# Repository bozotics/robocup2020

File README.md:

## PCB Design Files

View .sch and .brd files interactively on [Inventhub!](https://inventhub.io/c/bozotics/robocup2020/tree/PCB)   

Included in this repo are design files for the various PCBs we use. We designed these in EAGLE thanks to [Autodesk's free education licences](https://www.autodesk.com/education/free-software/featured). 

The libraries used unfortunately cannot be shared due to Autodesk's library.io sharing limitations, however if you would like to view it do contact us! We would be happy to send a copy of the latest version, albeit without the included 3d models (again due to the library.io limitations).

Structure of this repository:
```
.
├── Datasheets # PDFs for the various parts we use
├── PCB2k20 # Design files for our PCBs
│   ├── Layer 1, 3, 4 # for Soccer Open
│   ├── PMW3360MouseSensor # for our Mouse Sensor breakout board
│   ├── RescueLS # for Rescue Line's light sensor breakout board
│   └── TPS5430 # for the buck converter breakout board
├── TestV3_2020
└── Rescue
```
Files for previous years can be found in our [other archived repositories](https://github.com/bozotics).

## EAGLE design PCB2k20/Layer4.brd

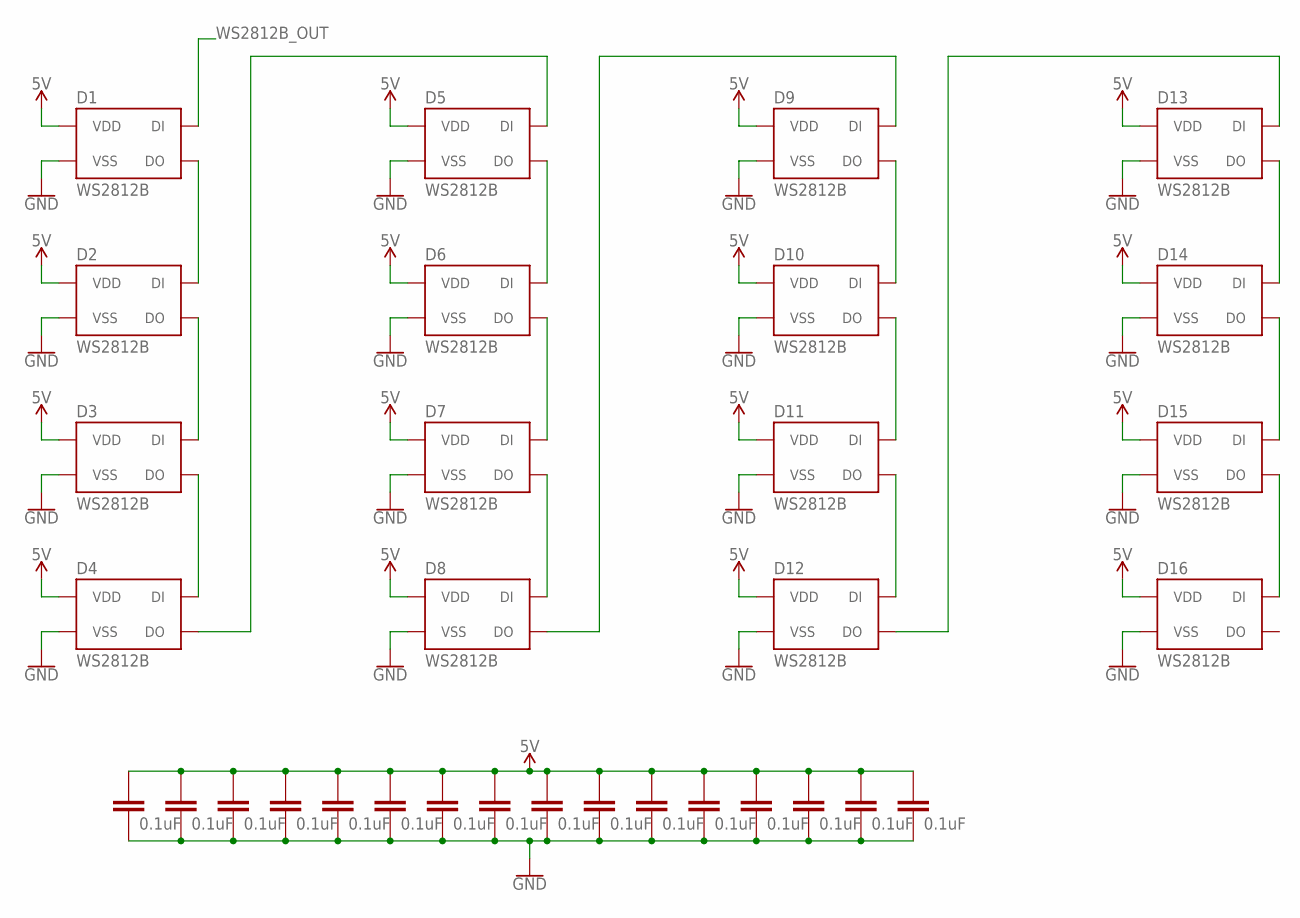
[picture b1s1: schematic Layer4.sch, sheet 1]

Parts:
AC1, AC2, AC3, AC4, AC5, AC6, AC7, AC8: 0.1uF; C0603
C1, C3, C5, C7, C9, C11, C13, C15: 0.1uF; C0603
D1, D2, D3, D4, D5, D6, D7, D8, D9, D10, D11, D12, D13, D14, D15, D16: WS2812B

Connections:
5V: AC1.1, AC2.1, AC3.1, AC4.1, AC5.1, AC6.1, AC7.1, AC8.1, C1.1, C3.1, C5.1, C7.1, C9.1, C11.1, C13.1, C15.1, D1.1 (VDD), D2.1 (VDD), D3.1 (VDD), D4.1 (VDD), D5.1 (VDD), D6.1 (VDD), D7.1 (VDD), D8.1 (VDD), D9.1 (VDD), D10.1 (VDD), D11.1 (VDD), D12.1 (VDD), D13.1 (VDD), D14.1 (VDD), D15.1 (VDD), D16.1 (VDD); also elsewhere on the board
GND: AC1.2, AC2.2, AC3.2, AC4.2, AC5.2, AC6.2, AC7.2, AC8.2, C1.2, C3.2, C5.2, C7.2, C9.2, C11.2, C13.2, C15.2, D1.3 (VSS), D2.3 (VSS), D3.3 (VSS), D4.3 (VSS), D5.3 (VSS), D6.3 (VSS), D7.3 (VSS), D8.3 (VSS), D9.3 (VSS), D10.3 (VSS), D11.3 (VSS), D12.3 (VSS), D13.3 (VSS), D14.3 (VSS), D15.3 (VSS), D16.3 (VSS); also elsewhere on the board
unnamed: D1.2 (DO), D2.4 (DI)
unnamed: D2.2 (DO), D3.4 (DI)
unnamed: D3.2 (DO), D4.4 (DI)
unnamed: D4.2 (DO), D5.4 (DI)
unnamed: D5.2 (DO), D6.4 (DI)
unnamed: D6.2 (DO), D7.4 (DI)
unnamed: D7.2 (DO), D8.4 (DI)
unnamed: D8.2 (DO), D9.4 (DI)
unnamed: D9.2 (DO), D10.4 (DI)
unnamed: D10.2 (DO), D11.4 (DI)
unnamed: D11.2 (DO), D12.4 (DI)
unnamed: D12.2 (DO), D13.4 (DI)
unnamed: D13.2 (DO), D14.4 (DI)
unnamed: D14.2 (DO), D15.4 (DI)
unnamed: D15.2 (DO), D16.4 (DI)
WS2812B_OUT: D1.4 (DI); also elsewhere on the board

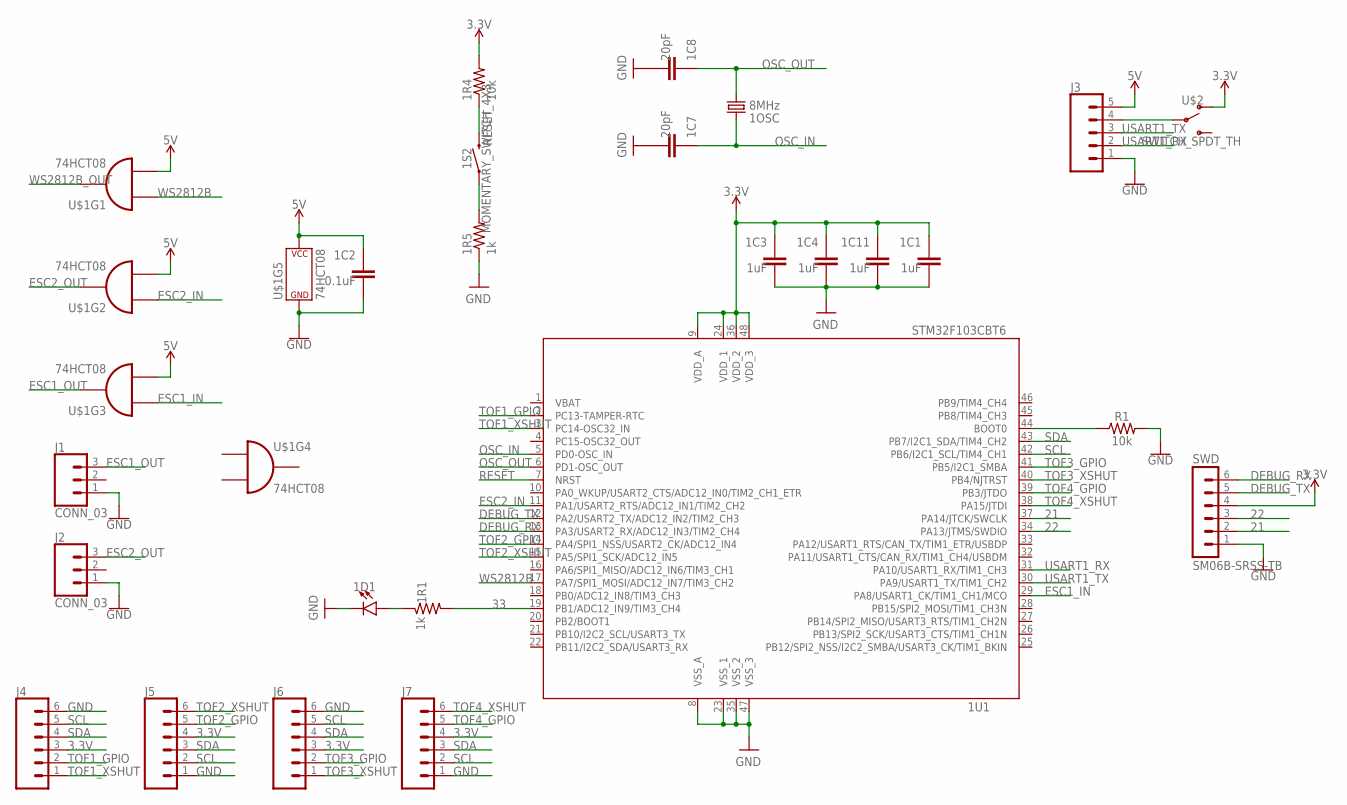
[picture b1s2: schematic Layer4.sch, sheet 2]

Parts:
1C1, 1C3, 1C4, 1C11: 1uF; C0603
1C2: 0.1uF; C0603
1C7, 1C8: 20pF; C0603
1D1: BLUE; LED-0603
1OSC: 8MHz; CRYSTAL-SMD-5X3.2-2PAD
1R1, 1R5: 1k; R0603
1R4: 10k; R0603
1S2: MOMENTARY_SWITCH_4X3
1U1: STM32F103CBT6; LQFP48
J1, J2: CONN_03; 1X03_LOCK
J3: CONN_05LOCK; 1X05_LOCK
J4, J5, J6, J7: CONN_06LOCK; 1X06_LOCK
R1: 10k; R0603
SWD: SM06B-SRSS-TB
U$1: 74HCT08; SOIC-14
U$2: SWITCH_SPDT_TH; SWITCH_SPDT_PTH_11.6X4.0MM_LOCK

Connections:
3.3V: 1C1.1, 1C3.1, 1C4.1, 1C11.1, 1R4.2, 1U1.9 (VDD_A), 1U1.24 (VDD_1), 1U1.36 (VDD_2), 1U1.48 (VDD_3), J4.3, J5.4, J6.3, J7.4, SWD.4, U$2.1 (O)
5V: 1C2.1, J3.5, U$1.P2 (I1), U$1.P5 (I1), U$1.P10 (I1), U$1.P14 (P$V+); also elsewhere on the board
21: 1U1.37 (PA14/JTCK/SWCLK), SWD.2
22: 1U1.34 (PA13/JTMS/SWDIO), SWD.3
33: 1R1.2, 1U1.19 (PB1/ADC12_IN9/TIM3_CH4)
DEBUG_RX: 1U1.13 (PA3/USART2_RX/ADC12_IN3/TIM2_CH4), SWD.6
DEBUG_TX: 1U1.12 (PA2/USART2_TX/ADC12_IN2/TIM2_CH3), SWD.5
ESC1_IN: 1U1.29 (PA8/USART1_CK/TIM1_CH1/MCO), U$1.P9 (I0)
ESC1_OUT: J1.3, U$1.P8 (O)
ESC2_IN: 1U1.11 (PA1/USART2_RTS/ADC12_IN1/TIM2_CH2), U$1.P4 (I0)
ESC2_OUT: J2.3, U$1.P6 (O)
GND: 1C1.2, 1C2.2, 1C3.2, 1C4.2, 1C7.2, 1C8.2, 1C11.2, 1D1.C, 1R5.1, 1U1.8 (VSS_A), 1U1.23 (VSS_1), 1U1.35 (VSS_2), 1U1.47 (VSS_3), J1.1, J2.1, J3.1, J4.6, J5.1, J6.6, J7.1, R1.2, SWD.1, U$1.P7 (P$V-); also elsewhere on the board
unnamed: 1D1.A, 1R1.1
unnamed: 1R5.2, 1S2.P$1 (1)
unnamed: 1U1.44 (BOOT0), R1.1
unnamed: J3.4, U$2.2
OSC_IN: 1C7.1, 1OSC.P$2 (2), 1U1.5 (PD0-OSC_IN)
OSC_OUT: 1C8.1, 1OSC.P$1 (1), 1U1.6 (PD1-OSC_OUT)
RESET: 1R4.1, 1S2.P$2 (2), 1U1.7 (NRST)
SCL: 1U1.42 (PB6/I2C1_SCL/TIM4_CH1), J4.5, J5.2, J6.5, J7.2
SDA: 1U1.43 (PB7/I2C1_SDA/TIM4_CH2), J4.4, J5.3, J6.4, J7.3
TOF1_GPIO: 1U1.2 (PC13-TAMPER-RTC), J4.2
TOF1_XSHUT: 1U1.3 (PC14-OSC32_IN), J4.1
TOF2_GPIO: 1U1.14 (PA4/SPI1_NSS/USART2_CK/ADC12_IN4), J5.5
TOF2_XSHUT: 1U1.15 (PA5/SPI1_SCK/ADC12_IN5), J5.6
TOF3_GPIO: 1U1.41 (PB5/I2C1_SMBA), J6.2
TOF3_XSHUT: 1U1.40 (PB4/NJTRST), J6.1
TOF4_GPIO: 1U1.39 (PB3/JTDO), J7.5
TOF4_XSHUT: 1U1.38 (PA15/JTDI), J7.6
USART1_RX: 1U1.31 (PA10/USART1_RX/TIM1_CH3), J3.2
USART1_TX: 1U1.30 (PA9/USART1_TX/TIM1_CH2), J3.3
VBAT: 1U1.1 (VBAT)
WS2812B: 1U1.17 (PA7/SPI1_MOSI/ADC12_IN7/TIM3_CH2), U$1.P1 (I0)
WS2812B_OUT: U$1.P3 (O); also elsewhere on the board

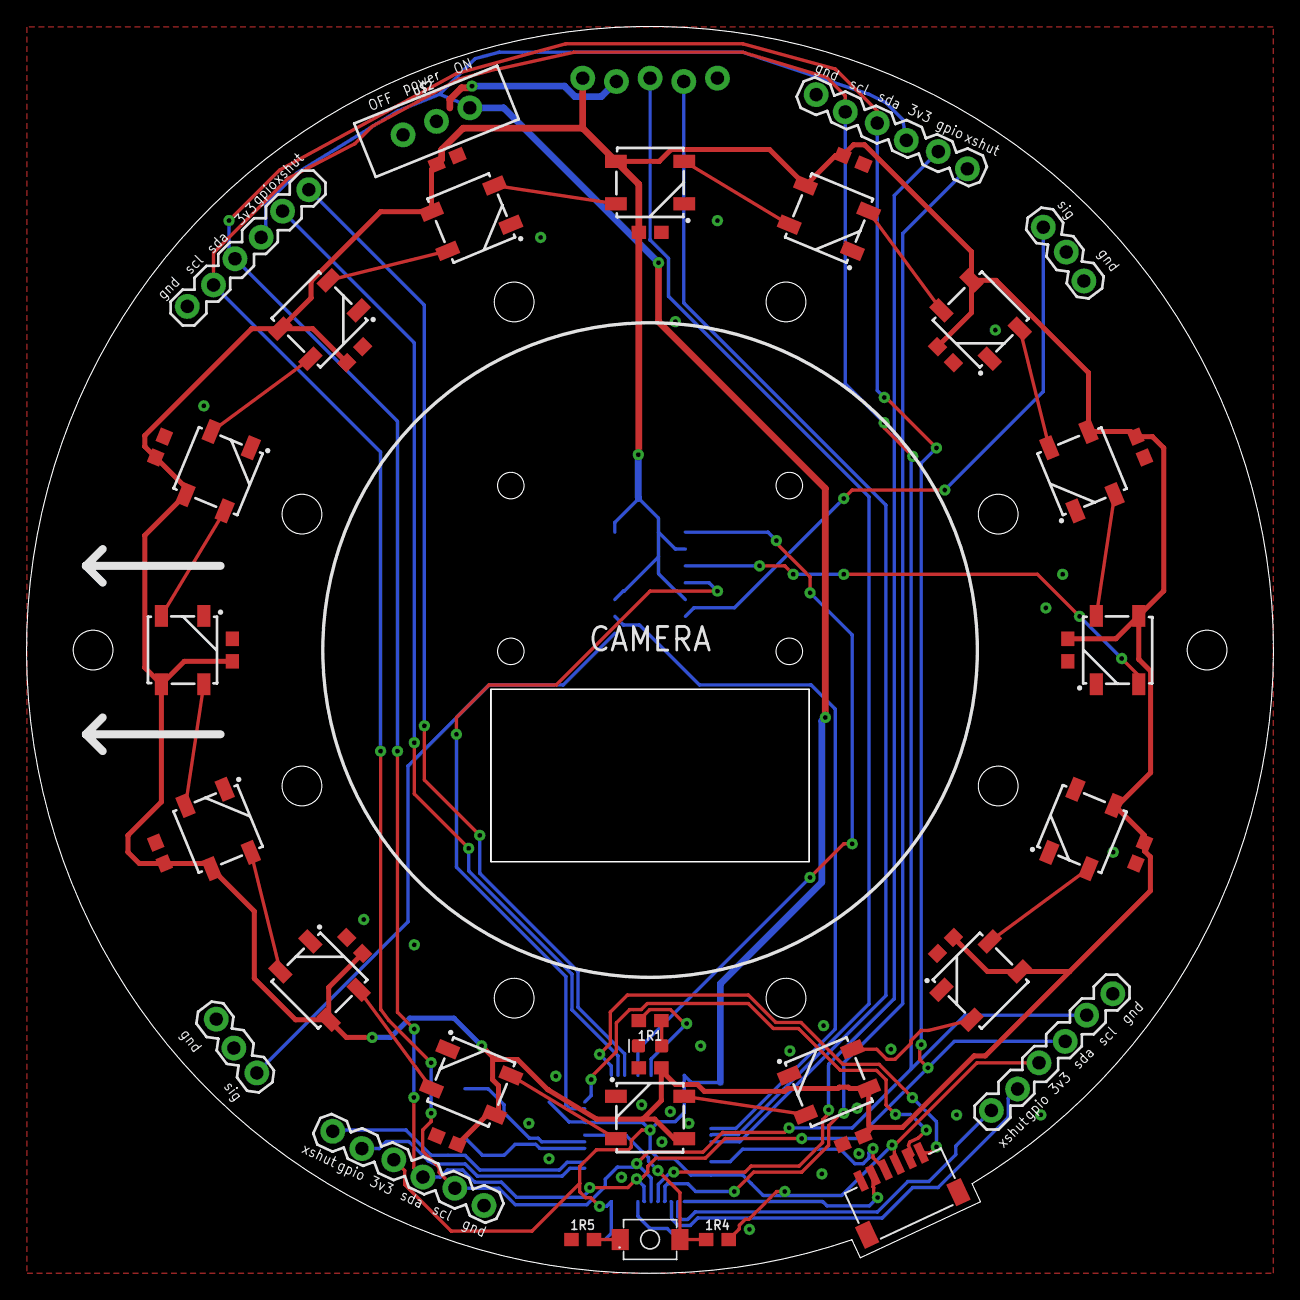
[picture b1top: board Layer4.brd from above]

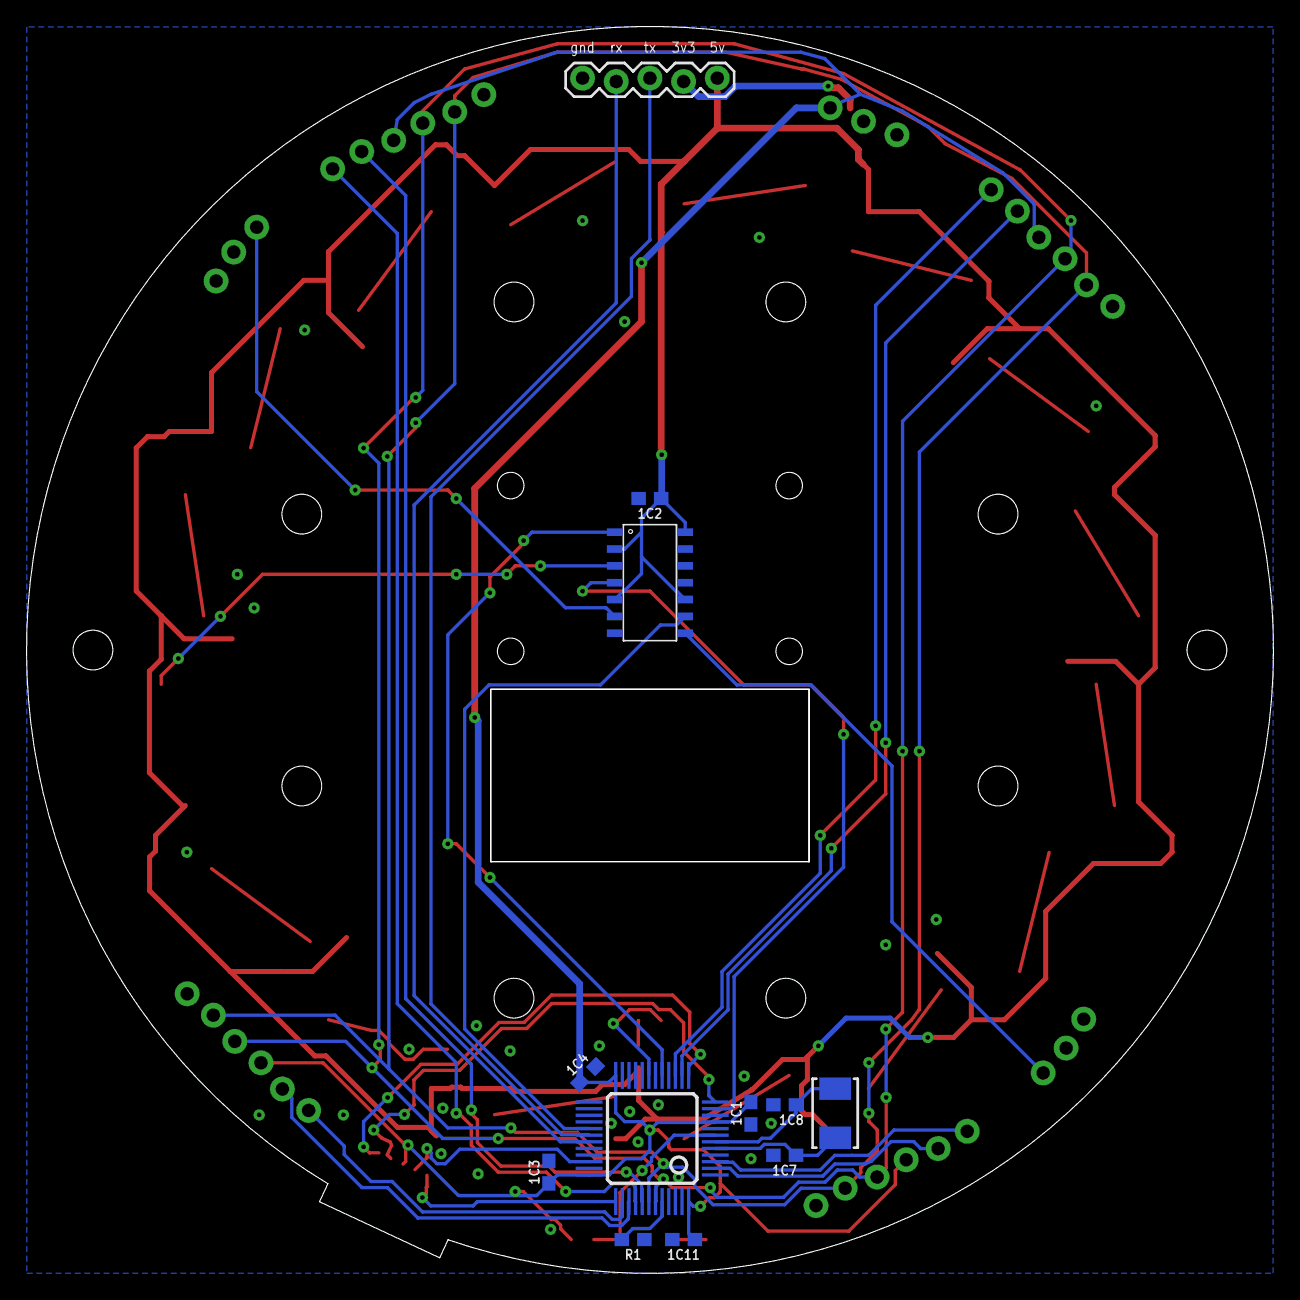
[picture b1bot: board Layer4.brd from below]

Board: 2 copper layers, 94.0 x 94.0 mm, 57 parts (12 on the bottom side), 48 nets.

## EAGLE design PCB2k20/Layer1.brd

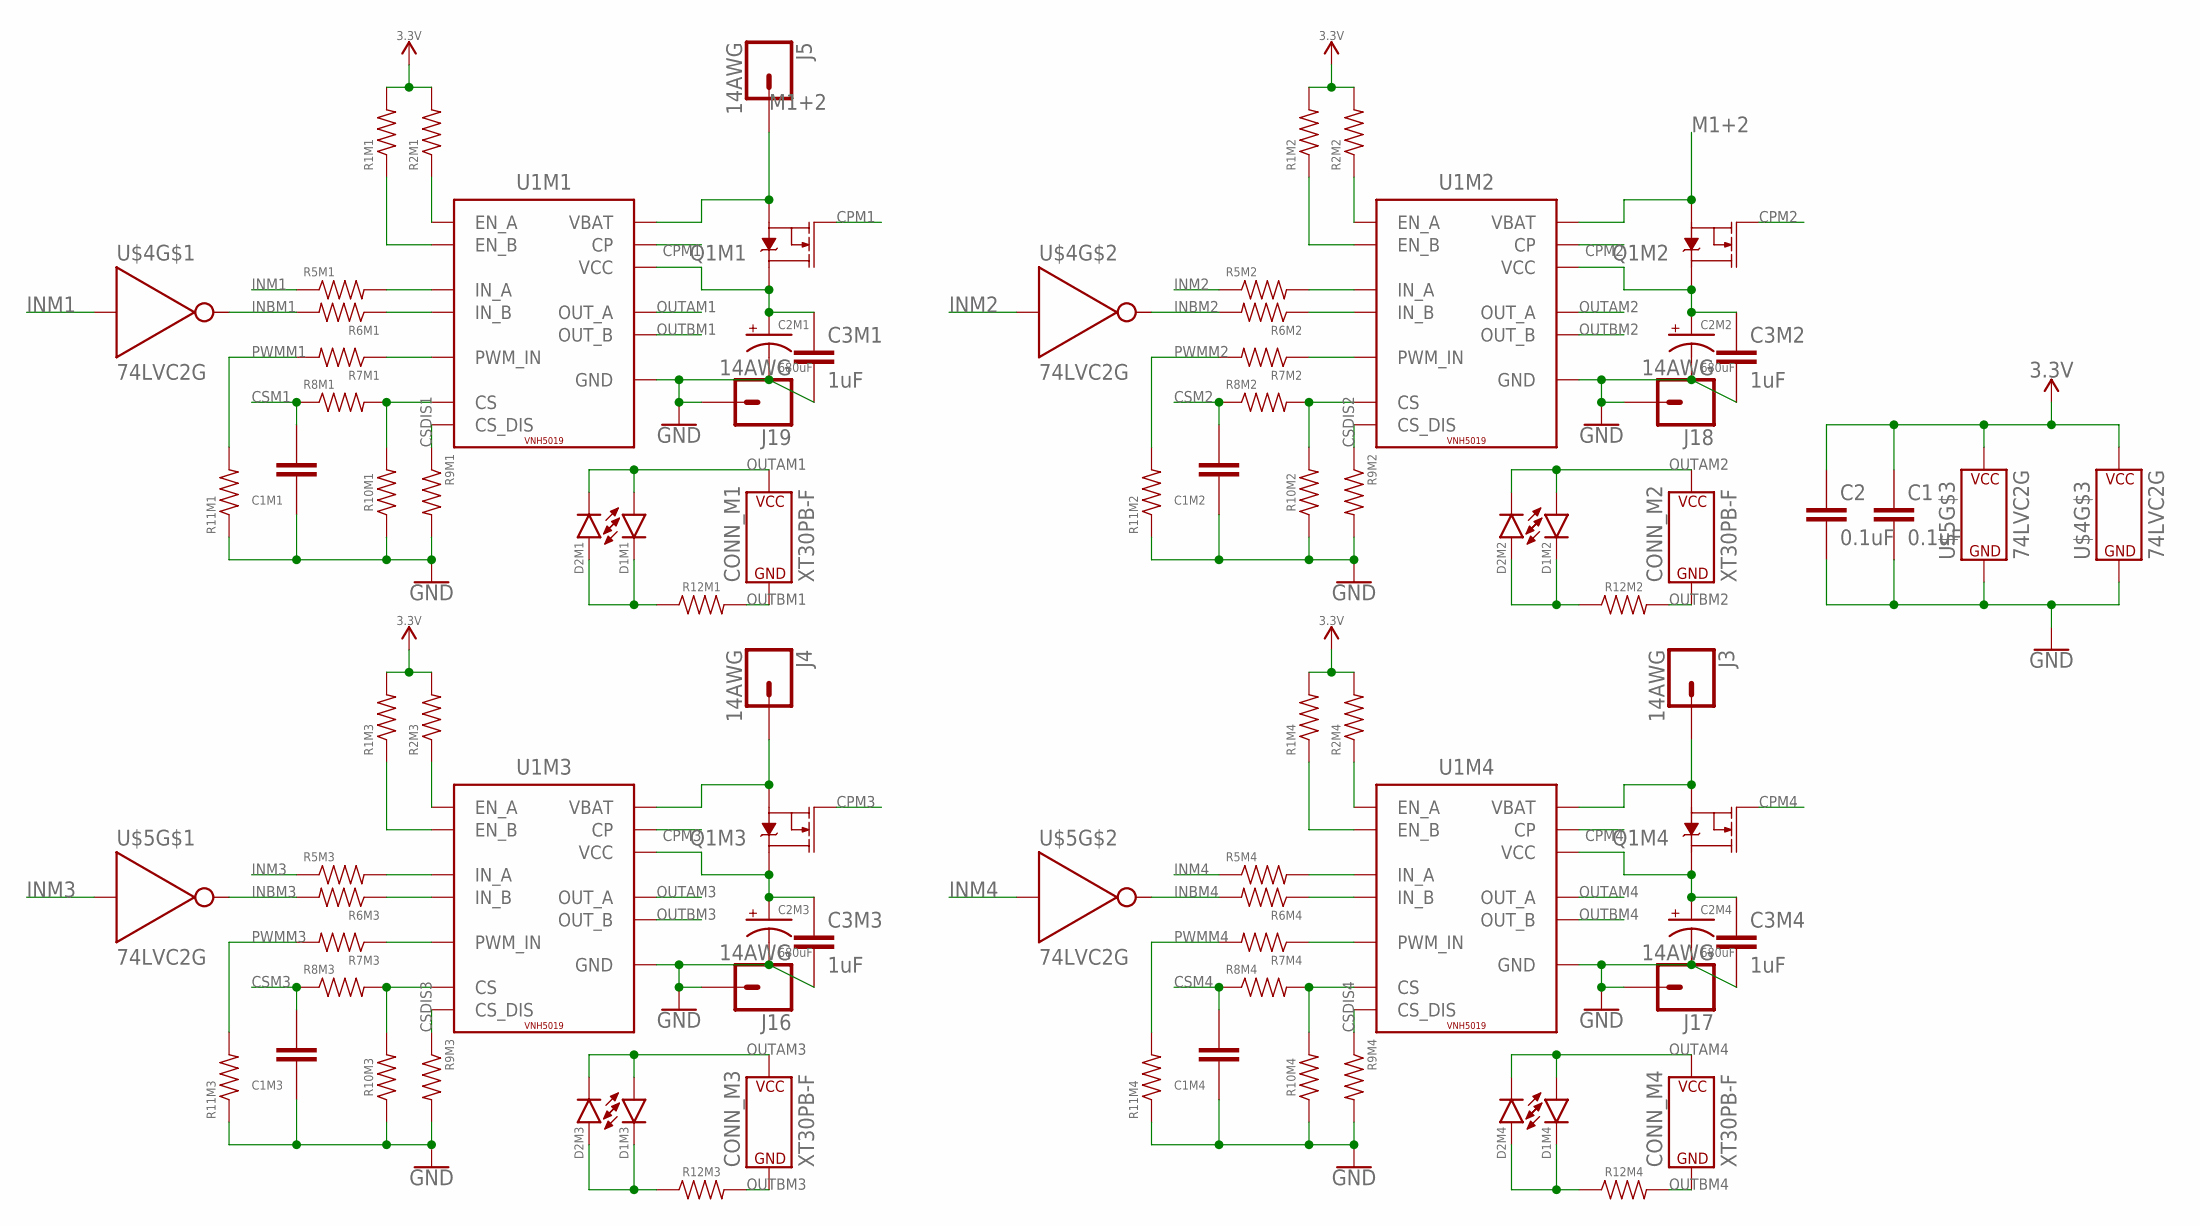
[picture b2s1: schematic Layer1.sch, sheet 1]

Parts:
C1, C2: 0.1uF; C0603
C1M1, C1M2, C1M3, C1M4: 33nF; C0603
C2M1, C2M2, C2M3, C2M4: 680uF; E3,5-8
C3M1, C3M2, C3M3, C3M4: 1uF; C0603
CONN_M1, CONN_M2, CONN_M3, CONN_M4: XT30PB-F
D1M1, D1M2, D1M3, D1M4: GREEN; LED-0603
D2M1, D2M2, D2M3, D2M4: RED; LED-0603
J3, J4, J5, J16, J17, J18, J19: 14AWG
Q1M1, Q1M2, Q1M3, Q1M4: AOD482; DPAK
R1M1, R1M2, R1M3, R1M4, R2M1, R2M2, R2M3, R2M4: 3.24k; R0603
R5M1, R5M2, R5M3, R5M4, R6M1, R6M2, R6M3, R6M4, R7M1, R7M2, R7M3, R7M4, R10M1, R10M2, R10M3, R10M4: 1k; R0603
R8M1, R8M2, R8M3, R8M4, R9M1, R9M2, R9M3, R9M4, R11M1, R11M2, R11M3, R11M4: 10k; R0603
R12M1, R12M2, R12M3, R12M4: 4.7k; R0603
U1M1, U1M2, U1M3, U1M4: VNH5019; POWERSO-30
U$4, U$5: 74LVC2G; SOT23-6

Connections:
3.3V: C1.1, C2.1, R1M1.2, R1M2.2, R1M3.2, R1M4.2, R2M1.2, R2M2.2, R2M3.2, R2M4.2, U$4.5 (P$V+), U$5.5 (P$V+); also elsewhere on the board
CPM1: Q1M1.1 (G), U1M1.P11 (CP)
CPM2: Q1M2.1 (G), U1M2.P11 (CP)
CPM3: Q1M3.1 (G), U1M3.P11 (CP)
CPM4: Q1M4.1 (G), U1M4.P11 (CP)
CSDIS1: R9M1.1, U1M1.P6 (CS_DIS)
CSDIS2: R9M2.1, U1M2.P6 (CS_DIS)
CSDIS3: R9M3.1, U1M3.P6 (CS_DIS)
CSDIS4: R9M4.1, U1M4.P6 (CS_DIS)
CSM1: C1M1.2, R8M1.1; also elsewhere on the board
CSM2: C1M2.2, R8M2.1; also elsewhere on the board
CSM3: C1M3.2, R8M3.1; also elsewhere on the board
CSM4: C1M4.2, R8M4.1; also elsewhere on the board
GND: C1.2, C1M1.1, C1M2.1, C1M3.1, C1M4.1, C2.2, C2M1.-, C2M2.-, C2M3.-, C2M4.-, C3M1.2, C3M2.2, C3M3.2, C3M4.2, J16.P$1, J17.P$1, J18.P$1, J19.P$1, R9M1.2, R9M2.2, R9M3.2, R9M4.2, R10M1.1, R10M2.1, R10M3.1, R10M4.1, R11M1.1, R11M2.1, R11M3.1, R11M4.1, U1M1.P18 (GND), U1M1.P19 (GND), U1M1.P20 (GND), U1M1.P26 (GND), U1M1.P27 (GND), U1M1.P28 (GND), U1M2.P18 (GND), U1M2.P19 (GND), U1M2.P20 (GND), U1M2.P26 (GND), U1M2.P27 (GND), U1M2.P28 (GND), U1M3.P18 (GND), U1M3.P19 (GND), U1M3.P20 (GND), U1M3.P26 (GND), U1M3.P27 (GND), U1M3.P28 (GND), U1M4.P18 (GND), U1M4.P19 (GND), U1M4.P20 (GND), U1M4.P26 (GND), U1M4.P27 (GND), U1M4.P28 (GND), U$4.2 (P$V-), U$5.2 (P$V-); also elsewhere on the board
INBM1: R6M1.2, U$4.6 (Y)
INBM2: R6M2.2, U$4.4 (Y)
INBM3: R6M3.2, U$5.6 (Y)
INBM4: R6M4.2, U$5.4 (Y)
INM1: R5M1.1, U$4.1 (A); also elsewhere on the board
INM2: R5M2.1, U$4.3 (A); also elsewhere on the board
INM3: R5M3.1, U$5.1 (A); also elsewhere on the board
INM4: R5M4.1, U$5.3 (A); also elsewhere on the board
M1+2: J5.P$1, Q1M1.3 (S), Q1M2.3 (S), U1M1.P12 (VBAT), U1M2.P12 (VBAT)
unnamed: J3.P$1, Q1M4.3 (S), U1M4.P12 (VBAT)
unnamed: J4.P$1, Q1M3.3 (S), U1M3.P12 (VBAT)
unnamed: C2M1.+, C3M1.1, Q1M1.4 (D), U1M1.P3 (VCC), U1M1.P13 (VCC), U1M1.P23 (VCC), U1M1.P$19 (VCC), U1M1.P$20 (VCC), U1M1.P$21 (VCC), U1M1.P$22 (VCC), U1M1.P$23 (VCC), U1M1.P$24 (VCC), U1M1.P$25 (VCC), U1M1.P$26 (VCC), U1M1.P$27 (VCC), U1M1.P$28 (VCC), U1M1.SLUG1 (VCC)
unnamed: R2M1.1, U1M1.P5 (EN_A)
unnamed: R5M1.2, U1M1.P4 (IN_A)
unnamed: R1M1.1, U1M1.P9 (EN_B)
unnamed: R6M1.1, U1M1.P10 (IN_B)
unnamed: R8M1.2, R10M1.2, U1M1.P8 (CS)
unnamed: R7M1.1, U1M1.P7 (PWM_IN)
unnamed: D1M2.C, D2M2.A, R12M2.1
unnamed: C2M2.+, C3M2.1, Q1M2.4 (D), U1M2.P3 (VCC), U1M2.P13 (VCC), U1M2.P23 (VCC), U1M2.P$19 (VCC), U1M2.P$20 (VCC), U1M2.P$21 (VCC), U1M2.P$22 (VCC), U1M2.P$23 (VCC), U1M2.P$24 (VCC), U1M2.P$25 (VCC), U1M2.P$26 (VCC), U1M2.P$27 (VCC), U1M2.P$28 (VCC), U1M2.SLUG1 (VCC)
unnamed: R2M2.1, U1M2.P5 (EN_A)
unnamed: R5M2.2, U1M2.P4 (IN_A)
unnamed: R1M2.1, U1M2.P9 (EN_B)
unnamed: R6M2.1, U1M2.P10 (IN_B)
unnamed: R8M2.2, R10M2.2, U1M2.P8 (CS)
unnamed: R7M2.1, U1M2.P7 (PWM_IN)
unnamed: D1M3.C, D2M3.A, R12M3.1
unnamed: C2M3.+, C3M3.1, Q1M3.4 (D), U1M3.P3 (VCC), U1M3.P13 (VCC), U1M3.P23 (VCC), U1M3.P$19 (VCC), U1M3.P$20 (VCC), U1M3.P$21 (VCC), U1M3.P$22 (VCC), U1M3.P$23 (VCC), U1M3.P$24 (VCC), U1M3.P$25 (VCC), U1M3.P$26 (VCC), U1M3.P$27 (VCC), U1M3.P$28 (VCC), U1M3.SLUG1 (VCC)
unnamed: R2M3.1, U1M3.P5 (EN_A)
unnamed: R5M3.2, U1M3.P4 (IN_A)
unnamed: R1M3.1, U1M3.P9 (EN_B)
unnamed: R6M3.1, U1M3.P10 (IN_B)
unnamed: R8M3.2, R10M3.2, U1M3.P8 (CS)
unnamed: R7M3.1, U1M3.P7 (PWM_IN)
unnamed: D1M4.C, D2M4.A, R12M4.1
unnamed: C2M4.+, C3M4.1, Q1M4.4 (D), U1M4.P3 (VCC), U1M4.P13 (VCC), U1M4.P23 (VCC), U1M4.P$19 (VCC), U1M4.P$20 (VCC), U1M4.P$21 (VCC), U1M4.P$22 (VCC), U1M4.P$23 (VCC), U1M4.P$24 (VCC), U1M4.P$25 (VCC), U1M4.P$26 (VCC), U1M4.P$27 (VCC), U1M4.P$28 (VCC), U1M4.SLUG1 (VCC)
unnamed: R2M4.1, U1M4.P5 (EN_A)
unnamed: R5M4.2, U1M4.P4 (IN_A)
unnamed: R1M4.1, U1M4.P9 (EN_B)
unnamed: R6M4.1, U1M4.P10 (IN_B)
unnamed: R8M4.2, R10M4.2, U1M4.P8 (CS)
unnamed: R7M4.1, U1M4.P7 (PWM_IN)
unnamed: D1M1.C, D2M1.A, R12M1.1
OUTAM1: CONN_M1.+ (P$V+), D1M1.A, D2M1.C, U1M1.P1 (OUT_A), U1M1.P25 (OUT_A), U1M1.P30 (OUT_A), U1M1.P$1 (OUT_A), U1M1.P$2 (OUT_A), U1M1.P$3 (OUT_A), U1M1.P$4 (OUT_A), U1M1.P$5 (OUT_A), U1M1.P$6 (OUT_A), U1M1.P$7 (OUT_A), U1M1.P$8 (OUT_A), U1M1.P$9 (OUT_A), U1M1.SLUG2 (OUT_A)
OUTAM2: CONN_M2.+ (P$V+), D1M2.A, D2M2.C, U1M2.P1 (OUT_A), U1M2.P25 (OUT_A), U1M2.P30 (OUT_A), U1M2.P$1 (OUT_A), U1M2.P$2 (OUT_A), U1M2.P$3 (OUT_A), U1M2.P$4 (OUT_A), U1M2.P$5 (OUT_A), U1M2.P$6 (OUT_A), U1M2.P$7 (OUT_A), U1M2.P$8 (OUT_A), U1M2.P$9 (OUT_A), U1M2.SLUG2 (OUT_A)
OUTAM3: CONN_M3.+ (P$V+), D1M3.A, D2M3.C, U1M3.P1 (OUT_A), U1M3.P25 (OUT_A), U1M3.P30 (OUT_A), U1M3.P$1 (OUT_A), U1M3.P$2 (OUT_A), U1M3.P$3 (OUT_A), U1M3.P$4 (OUT_A), U1M3.P$5 (OUT_A), U1M3.P$6 (OUT_A), U1M3.P$7 (OUT_A), U1M3.P$8 (OUT_A), U1M3.P$9 (OUT_A), U1M3.SLUG2 (OUT_A)
OUTAM4: CONN_M4.+ (P$V+), D1M4.A, D2M4.C, U1M4.P1 (OUT_A), U1M4.P25 (OUT_A), U1M4.P30 (OUT_A), U1M4.P$1 (OUT_A), U1M4.P$2 (OUT_A), U1M4.P$3 (OUT_A), U1M4.P$4 (OUT_A), U1M4.P$5 (OUT_A), U1M4.P$6 (OUT_A), U1M4.P$7 (OUT_A), U1M4.P$8 (OUT_A), U1M4.P$9 (OUT_A), U1M4.SLUG2 (OUT_A)
OUTBM1: CONN_M1.- (P$V-), R12M1.2, U1M1.P15 (OUT_B), U1M1.P16 (OUT_B), U1M1.P21 (OUT_B), U1M1.P$10 (OUT_B), U1M1.P$11 (OUT_B), U1M1.P$12 (OUT_B), U1M1.P$13 (OUT_B), U1M1.P$14 (OUT_B), U1M1.P$15 (OUT_B), U1M1.P$16 (OUT_B), U1M1.P$17 (OUT_B), U1M1.P$18 (OUT_B), U1M1.SLUG3 (OUT_B)
OUTBM2: CONN_M2.- (P$V-), R12M2.2, U1M2.P15 (OUT_B), U1M2.P16 (OUT_B), U1M2.P21 (OUT_B), U1M2.P$10 (OUT_B), U1M2.P$11 (OUT_B), U1M2.P$12 (OUT_B), U1M2.P$13 (OUT_B), U1M2.P$14 (OUT_B), U1M2.P$15 (OUT_B), U1M2.P$16 (OUT_B), U1M2.P$17 (OUT_B), U1M2.P$18 (OUT_B), U1M2.SLUG3 (OUT_B)
OUTBM3: CONN_M3.- (P$V-), R12M3.2, U1M3.P15 (OUT_B), U1M3.P16 (OUT_B), U1M3.P21 (OUT_B), U1M3.P$10 (OUT_B), U1M3.P$11 (OUT_B), U1M3.P$12 (OUT_B), U1M3.P$13 (OUT_B), U1M3.P$14 (OUT_B), U1M3.P$15 (OUT_B), U1M3.P$16 (OUT_B), U1M3.P$17 (OUT_B), U1M3.P$18 (OUT_B), U1M3.SLUG3 (OUT_B)
OUTBM4: CONN_M4.- (P$V-), R12M4.2, U1M4.P15 (OUT_B), U1M4.P16 (OUT_B), U1M4.P21 (OUT_B), U1M4.P$10 (OUT_B), U1M4.P$11 (OUT_B), U1M4.P$12 (OUT_B), U1M4.P$13 (OUT_B), U1M4.P$14 (OUT_B), U1M4.P$15 (OUT_B), U1M4.P$16 (OUT_B), U1M4.P$17 (OUT_B), U1M4.P$18 (OUT_B), U1M4.SLUG3 (OUT_B)
PWMM1: R7M1.2, R11M1.2; also elsewhere on the board
PWMM2: R7M2.2, R11M2.2; also elsewhere on the board
PWMM3: R7M3.2, R11M3.2; also elsewhere on the board
PWMM4: R7M4.2, R11M4.2; also elsewhere on the board

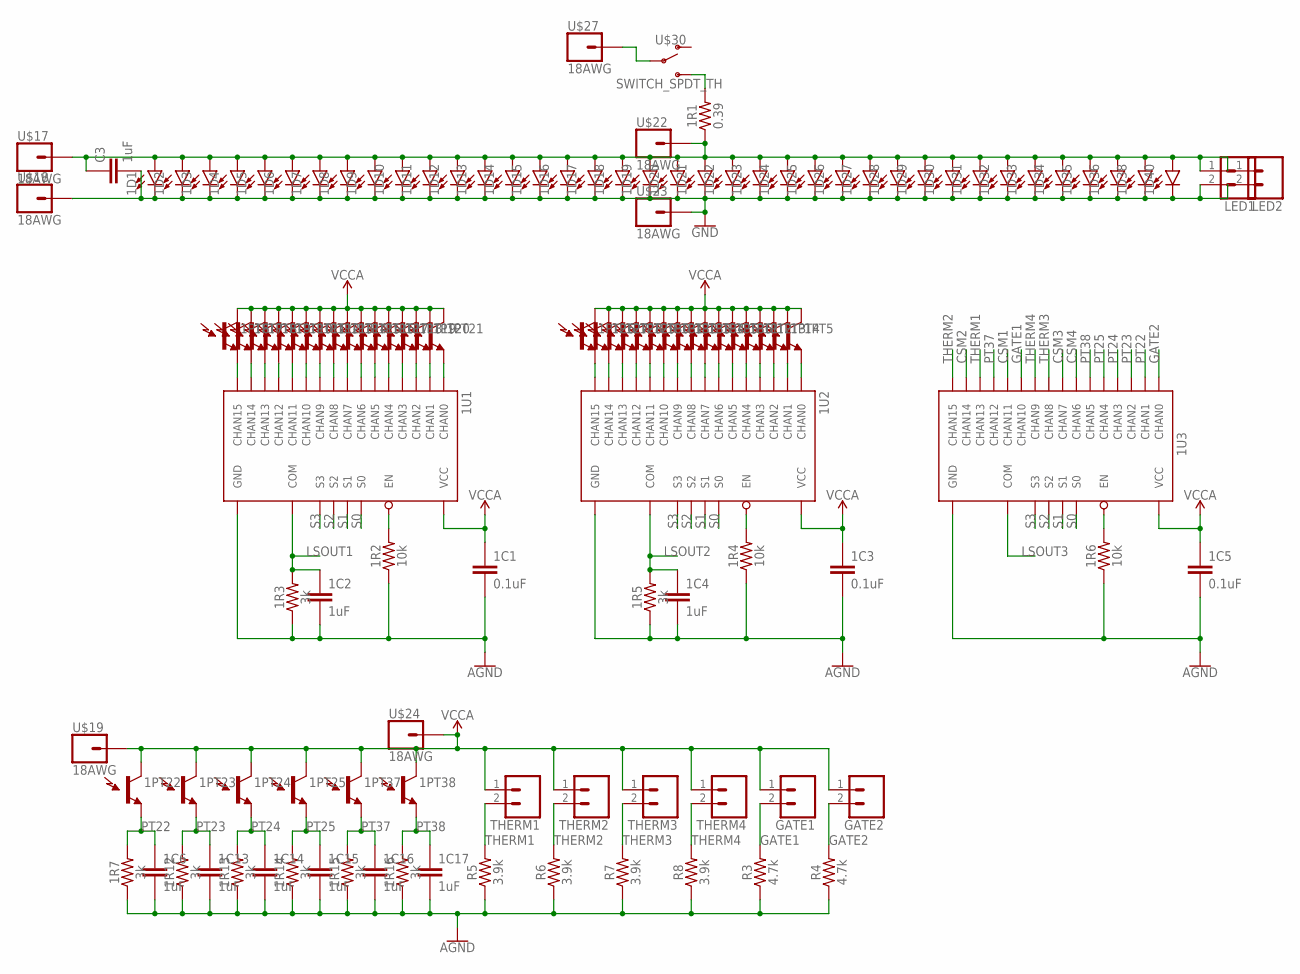
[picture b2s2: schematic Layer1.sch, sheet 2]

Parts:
1C1, 1C3, 1C5: 0.1uF; C0603
1C2, 1C4, 1C6, 1C13, 1C14, 1C15, 1C16, 1C17: 1uF; C0603
1D1, 1D2, 1D3, 1D4, 1D5, 1D6, 1D7, 1D8, 1D9, 1D10, 1D11, 1D12, 1D13, 1D14, 1D15, 1D16, 1D17, 1D18, 1D19, 1D20, 1D21, 1D22, 1D23, 1D24, 1D25, 1D26, 1D27, 1D28, 1D29, 1D30, 1D31, 1D32, 1D33, 1D34, 1D35, 1D36, 1D38, 1D40: 3528LED; 3528
1PT1, 1PT2, 1PT3, 1PT4, 1PT5, 1PT6, 1PT7, 1PT8, 1PT9, 1PT10, 1PT11, 1PT12, 1PT13, 1PT14, 1PT15, 1PT16, 1PT17, 1PT18, 1PT19, 1PT20, 1PT21, 1PT22, 1PT23, 1PT24, 1PT25, 1PT26, 1PT27, 1PT28, 1PT29, 1PT30, 1PT31, 1PT32, 1PT33, 1PT34, 1PT35, 1PT36, 1PT37, 1PT38: LIGHT_SENSOR_ALS; ALS-PT19
1R1: 0.39; R0603
1R2, 1R4, 1R6: 10k; R0603
1R3, 1R5, 1R7, 1R12, 1R13, 1R14, 1R15, 1R16: 3k; R0603
1U1, 1U2, 1U3: CD74HC4067SSOP-24; SSOP24
C3: 1uF; C0603
GATE1, GATE2: CONN_021X02_NO_SILK; 1X02_NO_SILK
LED1, LED2: CONN_021X02_NO_SILK; 1X02_NO_SILK
R3, R4: 4.7k; R0603
R5, R6, R7, R8: 3.9k; R0603
THERM1, THERM2, THERM3, THERM4: CONN_021X02_NO_SILK; 1X02_NO_SILK
U$17, U$18, U$19, U$22, U$23, U$24, U$27: 18AWG
U$30: SWITCH_SPDT_TH; SWITCH_SPDT_PTH_11.6X4.0MM_LOCK

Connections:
AGND: 1C1.2, 1C2.2, 1C3.2, 1C4.2, 1C5.2, 1C6.2, 1C13.2, 1C14.2, 1C15.2, 1C16.2, 1C17.2, 1R2.1, 1R3.1, 1R4.1, 1R5.1, 1R6.1, 1R7.1, 1R12.1, 1R13.1, 1R14.1, 1R15.1, 1R16.1, 1U1.12 (GND), 1U2.12 (GND), 1U3.12 (GND), R3.1, R4.1, R5.1, R6.1, R7.1, R8.1; also elsewhere on the board
CSM1: 1U3.20 (CHAN11); also elsewhere on the board
CSM2: 1U3.17 (CHAN14); also elsewhere on the board
CSM3: 1U3.2 (CHAN7); also elsewhere on the board
CSM4: 1U3.3 (CHAN6); also elsewhere on the board
GATE1: 1U3.21 (CHAN10), GATE1.2, R3.2
GATE2: 1U3.9 (CHAN0), GATE2.2, R4.2
GND: 1D1.C, 1D2.C, 1D3.C, 1D4.C, 1D5.C, 1D6.C, 1D7.C, 1D8.C, 1D9.C, 1D10.C, 1D11.C, 1D12.C, 1D13.C, 1D14.C, 1D15.C, 1D16.C, 1D17.C, 1D18.C, 1D19.C, 1D20.C, 1D21.C, 1D22.C, 1D23.C, 1D24.C, 1D25.C, 1D26.C, 1D27.C, 1D28.C, 1D29.C, 1D30.C, 1D31.C, 1D32.C, 1D33.C, 1D34.C, 1D35.C, 1D36.C, 1D38.C, 1D40.C, C3.2, LED1.2, LED2.2, U$18.P$1, U$23.P$1; also elsewhere on the board
LSOUT1: 1C2.1, 1R3.2, 1U1.1 (COM); also elsewhere on the board
LSOUT2: 1C4.1, 1R5.2, 1U2.1 (COM); also elsewhere on the board
LSOUT3: 1U3.1 (COM); also elsewhere on the board
unnamed: 1D1.A, 1D2.A, 1D3.A, 1D4.A, 1D5.A, 1D6.A, 1D7.A, 1D8.A, 1D9.A, 1D10.A, 1D11.A, 1D12.A, 1D13.A, 1D14.A, 1D15.A, 1D16.A, 1D17.A, 1D18.A, 1D19.A, 1D20.A, 1D21.A, 1D22.A, 1D23.A, 1D24.A, 1D25.A, 1D26.A, 1D27.A, 1D28.A, 1D29.A, 1D30.A, 1D31.A, 1D32.A, 1D33.A, 1D34.A, 1D35.A, 1D36.A, 1D38.A, 1D40.A, 1R1.1, C3.1, LED1.1, LED2.1, U$17.P$1, U$22.P$1
unnamed: 1PT26.E (E1), 1U2.16 (CHAN15)
unnamed: 1R1.2, U$30.3 (S)
unnamed: 1PT27.E (E1), 1U2.17 (CHAN14)
unnamed: 1PT28.E (E1), 1U2.18 (CHAN13)
unnamed: 1PT29.E (E1), 1U2.19 (CHAN12)
unnamed: 1PT30.E (E1), 1U2.20 (CHAN11)
unnamed: 1PT31.E (E1), 1U2.21 (CHAN10)
unnamed: 1PT32.E (E1), 1U2.22 (CHAN9)
unnamed: 1PT33.E (E1), 1U2.23 (CHAN8)
unnamed: 1PT34.E (E1), 1U2.2 (CHAN7)
unnamed: 1PT35.E (E1), 1U2.3 (CHAN6)
unnamed: 1PT36.E (E1), 1U2.4 (CHAN5)
unnamed: 1PT1.E (E1), 1U2.5 (CHAN4)
unnamed: 1PT2.E (E1), 1U2.6 (CHAN3)
unnamed: 1PT3.E (E1), 1U2.7 (CHAN2)
unnamed: 1PT4.E (E1), 1U2.8 (CHAN1)
unnamed: 1PT5.E (E1), 1U2.9 (CHAN0)
unnamed: 1PT6.E (E1), 1U1.16 (CHAN15)
unnamed: 1R2.2, 1U1.15 (EN)
unnamed: 1PT7.E (E1), 1U1.17 (CHAN14)
unnamed: 1PT8.E (E1), 1U1.18 (CHAN13)
unnamed: 1PT9.E (E1), 1U1.19 (CHAN12)
unnamed: 1PT10.E (E1), 1U1.20 (CHAN11)
unnamed: 1PT11.E (E1), 1U1.21 (CHAN10)
unnamed: 1PT12.E (E1), 1U1.22 (CHAN9)
unnamed: 1PT13.E (E1), 1U1.23 (CHAN8)
unnamed: 1PT14.E (E1), 1U1.2 (CHAN7)
unnamed: 1PT15.E (E1), 1U1.3 (CHAN6)
unnamed: 1PT16.E (E1), 1U1.4 (CHAN5)
unnamed: 1PT17.E (E1), 1U1.5 (CHAN4)
unnamed: 1PT18.E (E1), 1U1.6 (CHAN3)
unnamed: 1PT19.E (E1), 1U1.7 (CHAN2)
unnamed: 1PT20.E (E1), 1U1.8 (CHAN1)
unnamed: 1PT21.E (E1), 1U1.9 (CHAN0)
unnamed: U$27.P$1, U$30.2
unnamed: 1R4.2, 1U2.15 (EN)
unnamed: 1R6.2, 1U3.15 (EN)
PT22: 1C6.1, 1PT22.E (E1), 1R7.2, 1U3.8 (CHAN1)
PT23: 1C13.1, 1PT23.E (E1), 1R12.2, 1U3.7 (CHAN2)
PT24: 1C14.1, 1PT24.E (E1), 1R13.2, 1U3.6 (CHAN3)
PT25: 1C15.1, 1PT25.E (E1), 1R14.2, 1U3.5 (CHAN4)
PT37: 1C16.1, 1PT37.E (E1), 1R15.2, 1U3.19 (CHAN12)
PT38: 1C17.1, 1PT38.E (E1), 1R16.2, 1U3.4 (CHAN5)
S0: 1U1.10 (S0), 1U2.10 (S0), 1U3.10 (S0); also elsewhere on the board
S1: 1U1.11 (S1), 1U2.11 (S1), 1U3.11 (S1); also elsewhere on the board
S2: 1U1.14 (S2), 1U2.14 (S2), 1U3.14 (S2); also elsewhere on the board
S3: 1U1.13 (S3), 1U2.13 (S3), 1U3.13 (S3); also elsewhere on the board
THERM1: 1U3.18 (CHAN13), R5.2, THERM1.2
THERM2: 1U3.16 (CHAN15), R6.2, THERM2.2
THERM3: 1U3.23 (CHAN8), R7.2, THERM3.2
THERM4: 1U3.22 (CHAN9), R8.2, THERM4.2
VCCA: 1C1.1, 1C3.1, 1C5.1, 1PT1.C (C1), 1PT2.C (C1), 1PT3.C (C1), 1PT4.C (C1), 1PT5.C (C1), 1PT6.C (C1), 1PT7.C (C1), 1PT8.C (C1), 1PT9.C (C1), 1PT10.C (C1), 1PT11.C (C1), 1PT12.C (C1), 1PT13.C (C1), 1PT14.C (C1), 1PT15.C (C1), 1PT16.C (C1), 1PT17.C (C1), 1PT18.C (C1), 1PT19.C (C1), 1PT20.C (C1), 1PT21.C (C1), 1PT22.C (C1), 1PT23.C (C1), 1PT24.C (C1), 1PT25.C (C1), 1PT26.C (C1), 1PT27.C (C1), 1PT28.C (C1), 1PT29.C (C1), 1PT30.C (C1), 1PT31.C (C1), 1PT32.C (C1), 1PT33.C (C1), 1PT34.C (C1), 1PT35.C (C1), 1PT36.C (C1), 1PT37.C (C1), 1PT38.C (C1), 1U1.24 (VCC), 1U2.24 (VCC), 1U3.24 (VCC), GATE1.1, GATE2.1, THERM1.1, THERM2.1, THERM3.1, THERM4.1, U$19.P$1, U$24.P$1; also elsewhere on the board

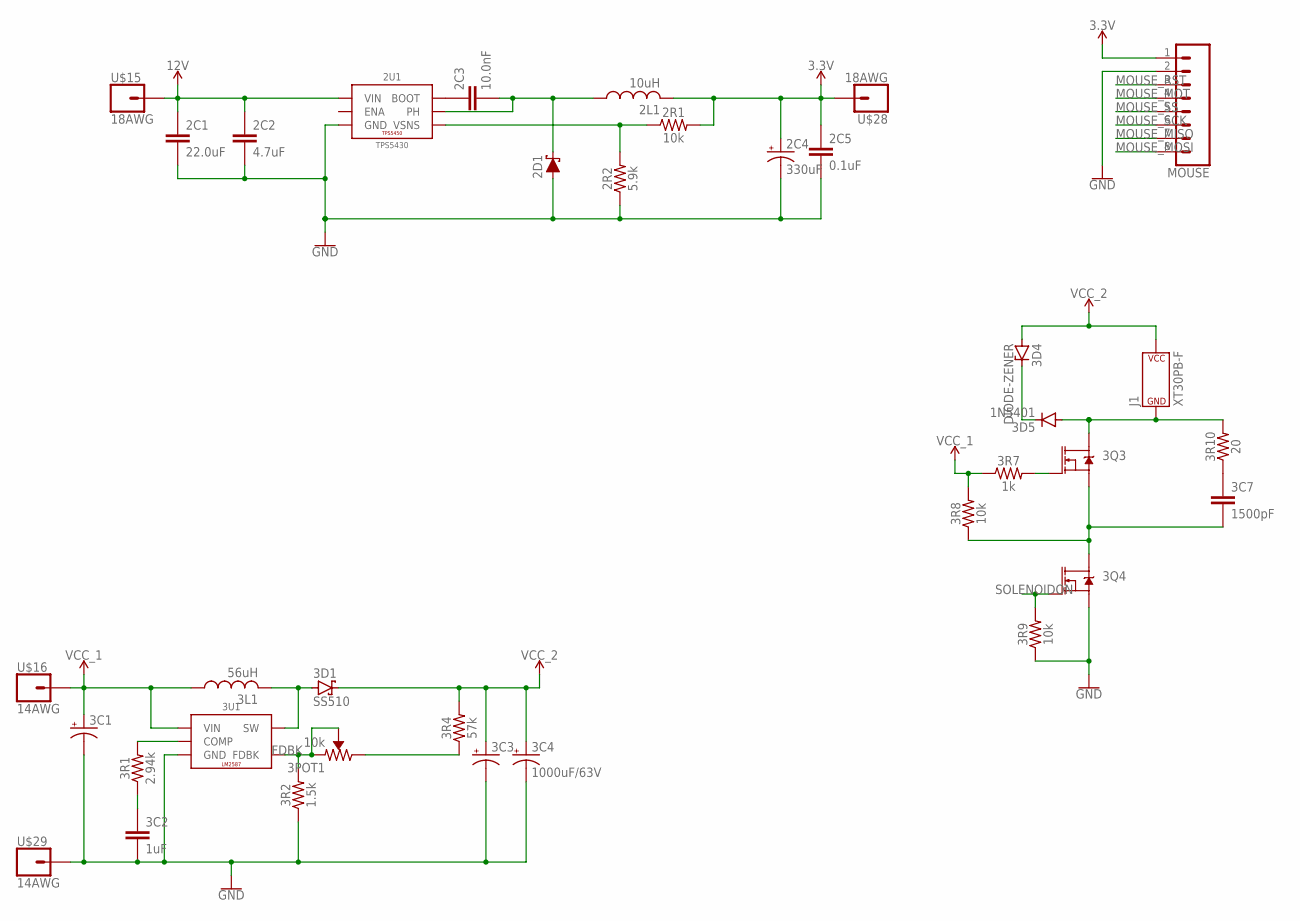
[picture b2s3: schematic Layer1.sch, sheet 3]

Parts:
2C1: 22.0uF; C1210
2C2: 4.7uF; C0603
2C3: 10.0nF; C0603
2C4: 330uF; D/7343-31R
2C5: 0.1uF; C0603
2D1: SS54; SMA-DIODE
2L1: 10uH; SWPA8040
2R1, 3R8, 3R9: 10k; R0603
2R2: 5.9k; R0603
2U1: TPS5430; POWERPAD-SOIC-8
3C1: 100uF; PANASONIC_D
3C2: 1uF; C0603
3C3: CAPACITOR_POL_10X10.5MM; 10X10.5_CAP
3C4: 1000uF/63V; 1000UF-CAP
3C7: 1500pF; C0603
3D1: SS510; SMB
3D4: DIODE-ZENER; DO41Z10
3D5: 1N5401; DO201-15
3L1: 56uH; CDRH127
3POT1: 10k; 3296-TRIMPOT
3Q3: STP75NF75; TO220V
3Q4: AO3400; SOT23-3
3R1: 2.94k; R0603
3R2: 1.5k; R0603
3R4: 57k; R0603
3R7: 1k; R0603
3R10: 20; R0603
3U1: LM2587; TO-263
J1: XT30PB-F
MOUSE: CONN_08LOCK; 1X08_LOCK
U$15, U$28: 18AWG
U$16, U$29: 14AWG

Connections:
3.3V: 2C4.+, 2C5.1, 2L1.P2 (2), 2R1.2, MOUSE.1, U$28.P$1; also elsewhere on the board
12V: 2C1.1, 2C2.1, 2U1.7 (VIN), U$15.P$1
FDBK: 3POT1.1 (CCW), 3POT1.2 (WIPER), 3R2.2, 3U1.P2 (FDBK)
GND: 2C1.2, 2C2.2, 2C4.-, 2C5.2, 2D1.A, 2R2.1, 2U1.6 (GND), 2U1.9 (GND), 2U1.P$1 (GND), 2U1.P$2 (GND), 2U1.P$3 (GND), 2U1.P$4 (GND), 2U1.P$5 (GND), 2U1.P$6 (GND), 3C1.-, 3C2.2, 3C3.-, 3C4.-, 3Q4.2 (S), 3R2.1, 3R9.1, 3U1.P3 (GND), 3U1.P$1 (GND), 3U1.P$2 (GND), 3U1.P$3 (GND), 3U1.P$4 (GND), 3U1.P$5 (GND), 3U1.P$6 (GND), 3U1.P$7 (GND), 3U1.P$8 (GND), 3U1.P$9 (GND), 3U1.P$10 (GND), 3U1.P$11 (GND), 3U1.P$12 (GND), 3U1.P$13 (GND), 3U1.P$14 (GND), 3U1.P$15 (GND), 3U1.P$16 (GND), 3U1.P$17 (GND), 3U1.P$18 (GND), 3U1.P$19 (GND), 3U1.P$20 (GND), 3U1.TAB (GND), MOUSE.2, U$29.P$1; also elsewhere on the board
MOUSE_MISO: MOUSE.7; also elsewhere on the board
MOUSE_MOSI: MOUSE.8; also elsewhere on the board
MOUSE_MOT: MOUSE.4; also elsewhere on the board
MOUSE_RST: MOUSE.3; also elsewhere on the board
MOUSE_SCK: MOUSE.6; also elsewhere on the board
MOUSE_SS: MOUSE.5; also elsewhere on the board
unnamed: 3POT1.3 (CW), 3R4.1
unnamed: 3D1.A, 3L1.2, 3U1.P4 (SW)
unnamed: 3R1.2, 3U1.P1 (COMP)
unnamed: 3C2.1, 3R1.1
unnamed: 3C7.2, 3Q3.3 (S), 3Q4.3 (D), 3R8.1
unnamed: 3Q3.1 (G), 3R7.2
unnamed: 3D4.C, 3D5.C
unnamed: 2C3.2, 2D1.C, 2L1.P1 (1), 2U1.8 (PH)
unnamed: 2R1.1, 2R2.2, 2U1.4 (VSNS)
unnamed: 2C3.1, 2U1.1 (BOOT)
unnamed: 3C7.1, 3R10.1
SOLENOIDGND: 3D5.A, 3Q3.2 (D), 3R10.2, J1.- (P$V-)
SOLENOIDON: 3Q4.1 (G), 3R9.2; also elsewhere on the board
VCC_1: 3C1.+, 3L1.1, 3R7.1, 3R8.2, 3U1.P5 (VIN), U$16.P$1
VCC_2: 3C3.+, 3C4.+, 3D1.C, 3D4.A, 3R4.2, J1.+ (P$V+)

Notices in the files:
parts and their libraries:
SparkFun-Connectors: Licensing: Creative Commons ShareAlike 4.0 International - https://creativecommons.org/licenses/by-sa/4.0
